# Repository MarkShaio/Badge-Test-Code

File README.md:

Badge-Test-Code
===============
1.All the code here is from openbeacon except an added section in main.c under MSP430_tag directory. Find the do while loop. 
This is where all the checking code lives in. The code currently in the loop is meant to check the joint between the cpu and the 
accelerometer. This code may not work so you must check.

2.The code in comments in the loop works fine. Basically if you run the code and you see LED2 light up then that means at least one of the pins
from the SPI is not connected properly .

3.debug1.ino will let you check whether your switch is working. The LED on board should toggle along with the switch.

4.In "Latest PCB Version", you will find the most up to date version of my board. If you want to use it there is one thing that you need to 
change. The bottom right corner of the switch must not be covered by the ground plane. So remove the ground plane on the right side
and recreate that ground plane.

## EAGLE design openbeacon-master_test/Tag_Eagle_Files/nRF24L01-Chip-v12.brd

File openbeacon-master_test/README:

Here are the files used in my low cost deployment of the Openbeacon system. 
Most of the code belongs to their respective owners. This is simply a fork of many repositories which I changed to run on alternate hardware.

Crosstools-ng: These are the settings used to create the toolchain targeting the AT91SAM7 for building the basesation files. This file is used by the crosstool-ng toolchain builder. If it fails to load due to version issues you may have to manually insert the settings by opening the file with a text editor. 

Driver: This is the windows driver for the COM port used by the base station.

MSP430_Tag: These are the files running on the MSP430 together with the nRF24l01+ which make up the tag.

Netduino(at91sam7)_Basestation: This contains the base station code to be run on the netduino together with the nRF24l01+ radio package. 

Node-Server: This is a javascript server run by Node.js which listen on the UDP port for traffic and publishes data on MQTT. 

Openamd-localiser: This is a fork of the localised software used in the opened conference. It has been modified such that it can listen to traffic on MQTT and republish the data back on another MQTT channel.Use options -M and -Q when launching to enable mqtt. Look at 'estimator.c' for more info.

Tag Eagle Files: These are work in progress, non-tested eagle tag files.

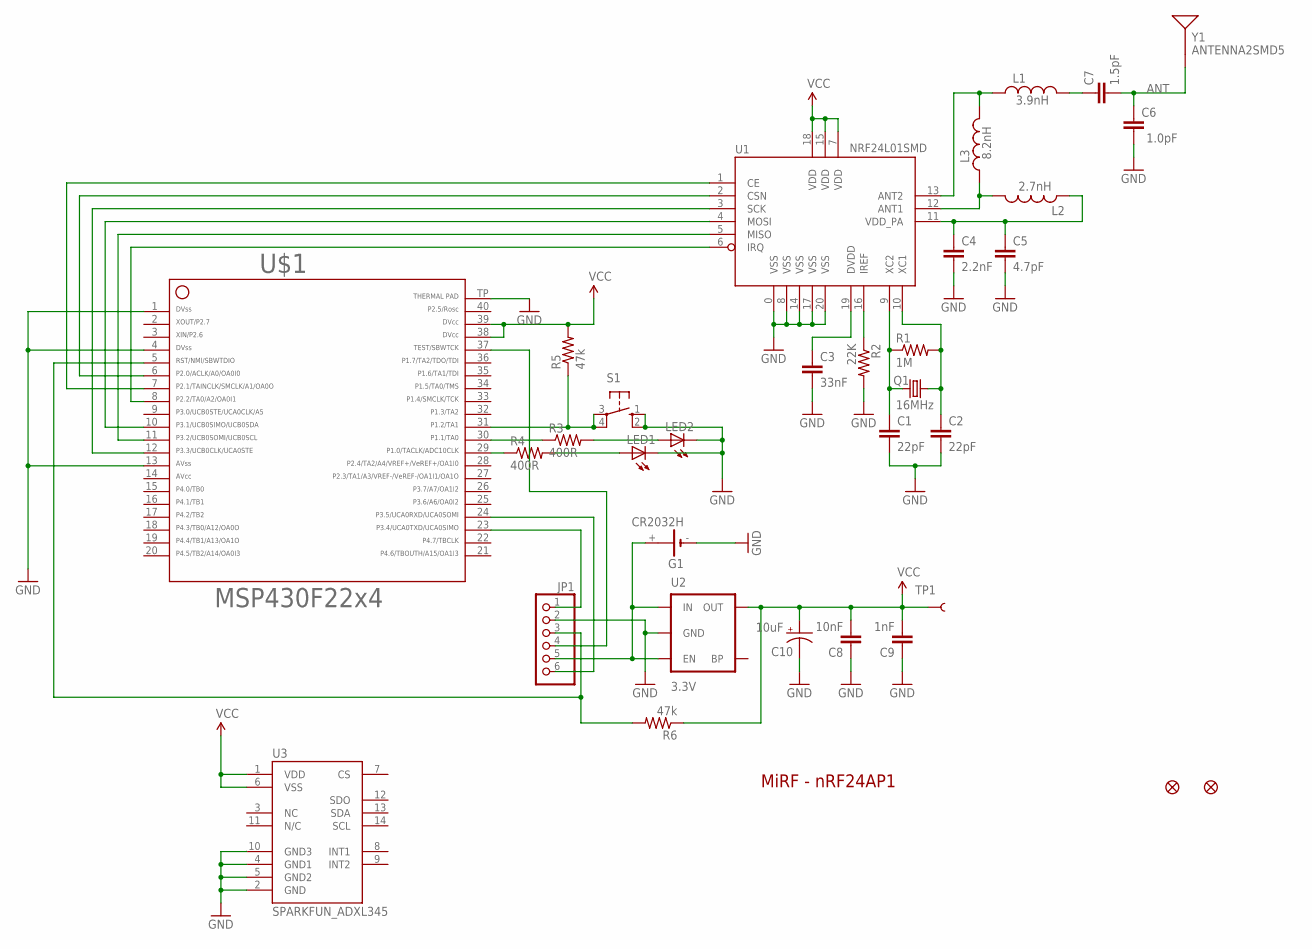
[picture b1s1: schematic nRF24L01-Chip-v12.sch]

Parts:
C1, C2: 22pF; C0402
C3: 33nF; C0402
C4: 2.2nF; C0402
C5: 4.7pF; C0402
C6: 1.0pF; C0402
C7: 1.5pF; C0402
C8: 10nF; C0402
C9: 1nF; C0402
C10: 10uF; EIA3216
G1: CR2032H
JP1: PINHD-1X6; 1X06
L1: 3.9nH; C0402
L2: 2.7nH; C0402
L3: 8.2nH; C0402
LED1, LED2: LEDCHIPLED_0805; CHIPLED_0805
Q1: 16MHz; CRYSTAL-SMD-5X3
R1: 1M; C0402
R2: 22K; C0402
R3, R4: 400R; C0402
R5, R6: 47k; C0402
S1: 10-XX; B3F-10XX
TP1: TEST-POINT3X5; PAD.03X.05
U1: NRF24L01SMD; QFN20
U2: 3.3V; SOT23-5
U3: SPARKFUN_ADXL345; SPARKFUN_LGA14
U$1: F22X4---RHA40; RHA40
U$2, U$3: FIDUCIAL1X2; FIDUCIAL-1X2
Y1: ANTENNA2SMD5; ANTENNA-CHIP5

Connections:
14: U$1.14
ANT: C6.2, C7.2, Y1.FEED
GND: C1.2, C2.2, C3.2, C4.2, C5.2, C6.1, C8.1, C9.1, C10.C (-), G1.-, JP1.2, LED1.C, LED2.C, R2.2, S1.1 (S), S1.2 (S1), U1.0 (VSS), U1.8 (VSS), U1.14 (VSS), U1.17 (VSS), U1.20 (VSS), U2.2 (GND), U3.2 (GND), U3.4 (GND1), U3.5 (GND2), U3.10 (GND3), U$1.1, U$1.4, U$1.13, U$1.TP
unnamed: C1.1, Q1.1, R1.1, U1.9 (XC2)
unnamed: C2.1, Q1.3 (2), R1.2, U1.10 (XC1)
unnamed: L2.2, L3.1, U1.12 (ANT1)
unnamed: R2.1, U1.16 (IREF)
unnamed: C3.1, U1.19 (DVDD)
unnamed: L1.1, L3.2, U1.13 (ANT2)
unnamed: C4.1, C5.1, L2.1, U1.11 (VDD_PA)
unnamed: U1.4 (MOSI), U$1.10
unnamed: C7.1, L1.2
unnamed: U1.5 (MISO), U$1.11
unnamed: U1.3 (SCK), U$1.12
unnamed: U1.2 (CSN), U$1.6
unnamed: U1.1 (CE), U$1.7
unnamed: R4.1, U$1.29
unnamed: U1.6 (IRQ), U$1.8
unnamed: R3.1, U$1.30
unnamed: LED2.A, R3.2
unnamed: LED1.A, R4.2
unnamed: R5.1, S1.3, S1.4 (P1), U$1.31
unnamed: JP1.1, U$1.23
unnamed: JP1.6, U$1.24
unnamed: JP1.4, U$1.37
unnamed: JP1.3, R6.2, U$1.5
RAW: G1.+, JP1.5, U2.1 (IN), U2.3 (EN)
VCC: C8.2, C9.2, C10.A (+), R5.2, R6.1, TP1.P$1, U1.7 (VDD), U1.15 (VDD), U1.18 (VDD), U2.5 (OUT), U3.1 (VDD), U3.6 (VSS), U$1.38, U$1.39

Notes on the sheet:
MiRF - nRF24AP1

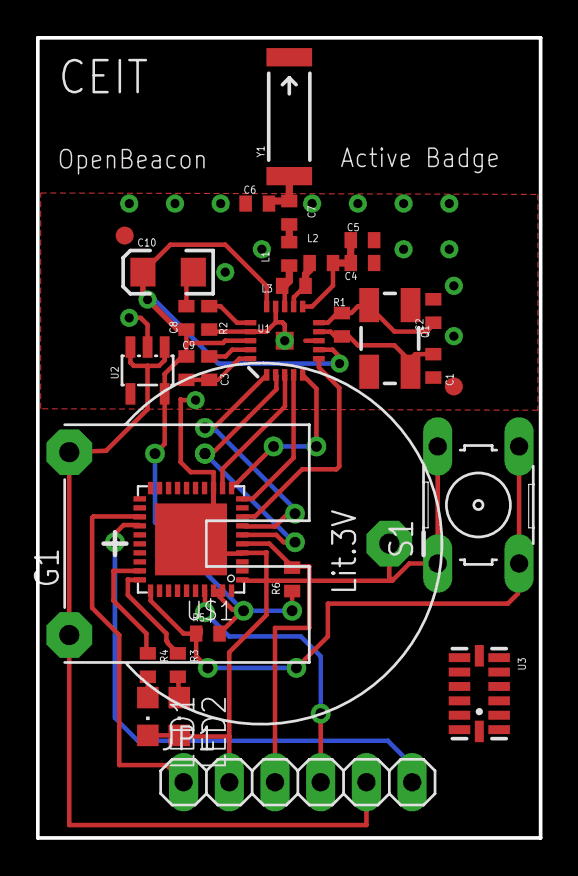
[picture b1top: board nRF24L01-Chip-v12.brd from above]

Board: 2 copper layers, 27.9 x 44.5 mm, 33 parts (1 on the bottom side), 27 nets.

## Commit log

2013-02-12 initial commit and also mark is silly
2013-02-12 Added test file for switches.
2013-02-12 File for switch testing
2013-02-12 Changed README content
